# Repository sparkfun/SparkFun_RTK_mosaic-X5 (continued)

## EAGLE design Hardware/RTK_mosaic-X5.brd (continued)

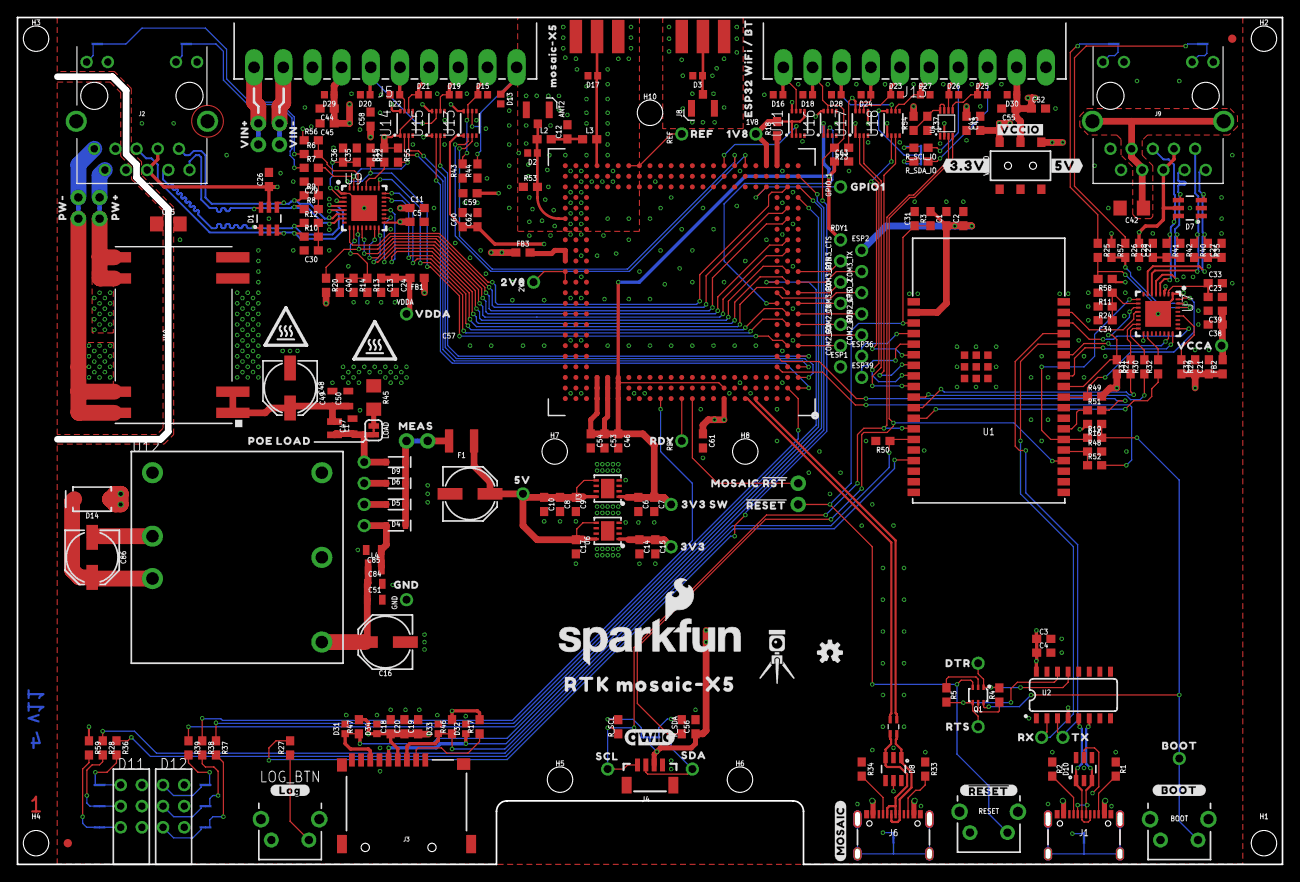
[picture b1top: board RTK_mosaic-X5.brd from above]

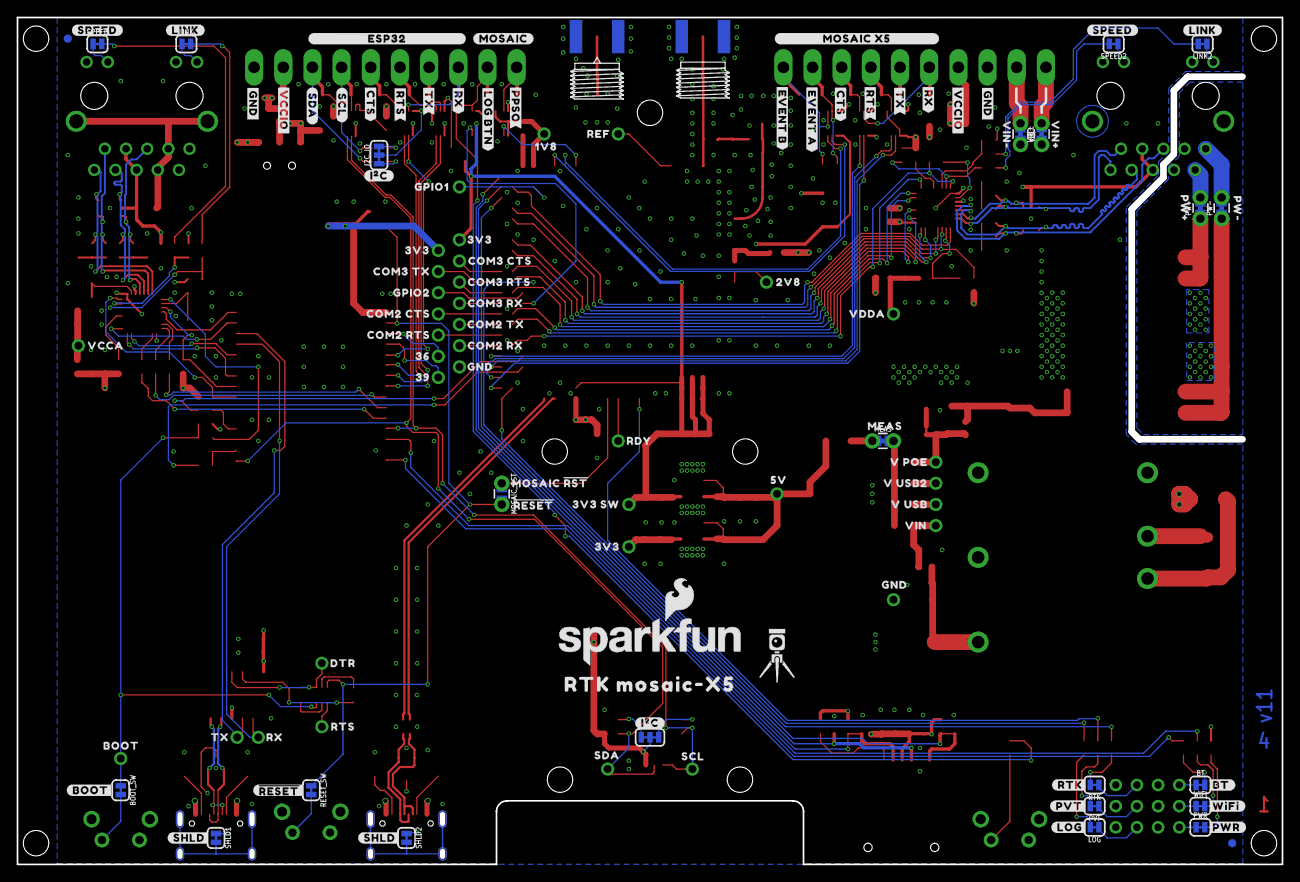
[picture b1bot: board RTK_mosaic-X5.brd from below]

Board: 4 copper layers, 151.8 x 101.6 mm, 408 parts (108 on the bottom side), 184 nets.

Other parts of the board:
LOGO2: QWIIC_LOGO_6MM; QWIIC_6MM
LOGO7: SFE_LOGO_NAME.2_INCH; SFE_LOGO_NAME_.2
LOGO8: SFE_LOGO_FLAME.2_INCH; SFE_LOGO_FLAME_.2
U$2: MOSAIC#X50
U$3, U$45: #SHLD#0
U$4, U$74: #RESET#0
U$5, U$113: PW#0
U$6, U$114: PW#1
U$7: ##RESET##5
U$8, U$46: #I�C#0
U$9, U$73: MOSAIC_#RST#6
U$10, U$120: #LINK#1
U$11: #LOG#4
U$12: #PVT#2
U$13: #RTK#3
U$14: #BT#2
U$15: #BOOT#6
U$16: #_______________MOSAIC_X5_______________#8
U$17, U$31: #RX#2
U$18, U$32: #TX#3
U$19, U$29: #RTS#4
U$20, U$30: #CTS#5
U$21: ESP32_WIFI_#_BT0
U$22: #EVENT_A#6
U$23: #EVENT_B#7
U$24, U$107: VCCA0
U$25, U$28: #GND#0
U$26, U$27, U$100: #VCCIO#1
U$33: #PPSO#11
U$34: #LOG_BTN#33
U$35: #SCL#10
U$36: #SDA#9
U$37, U$119: #MOSAIC#8
U$38: #___________________ESP32___________________#34
U$39: #3#3V#6
U$40: #5V#0
U$41, U$42: 2V8220
U$43, U$44: BOOT2
U$47: COM2_CTS219
U$48: COM2_RTS219
U$49: COM2_RX219
U$54: COM2_TX219
U$55, U$76: RTS2231
U$56, U$77: DTR2232
U$57: COM3_CTS18
U$58: COM3_RTS18
U$59, U$88: 3V3_SW25
U$60, U$87: 3V325
U$61, U$86: 5V25
U$62, U$84: MEAS2
U$63, U$70: VIN#0
U$64: COM3_RX219
U$65: COM3_TX18
U$66, U$67: GPIO17
U$68: GPIO218
U$69, U$99: RTK_MOSAIC#X50
U$71, U$72: VIN#1
U$75, U$78: RDY5
U$79, U$80: REF219
U$81: V_POE0
U$82: V_USB3
U$83: V_USB24
U$85: VIN1
U$89, U$90: RX0
U$91, U$92: SCL3
U$93, U$94: SDA4
U$95, U$96: TX1
U$97, U$98: VDDA220
U$101, U$102: 1V80
U$103: #PWR#0
U$104: #WIFI#1
U$105: 360
U$106: 39361
U$108: GND39362
U$109, U$110: 3V339362
U$116: #_LOG_#5
U$117: #_#RESET#_#0
U$118: #_BOOT_#1
U$121, U$122: #SPEED#0
U$135, U$143: GND12
U$136: POE_LOAD0
U$146, U$147: HIGH_TEMP_WARNING
U$152, U$153: RTK5#SVG0

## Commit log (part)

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2023-07-18 Ready for airwire review
2023-07-19 Silk added. Layer 15 polygon is now GND.
2023-07-19 Routed
2023-07-20 Tweaked and panelized
2023-07-20 Add panels
2023-07-20 Correct Ethernet PHY pad numbering. Needs re-panelizing
2023-07-21 Add second antenna connector for future mosaic-H product
2023-07-21 Adding u.FL connector for mosaic-H - with standoff holes for a u.FL-SMA daughter board
2023-07-24 Add Phy PROD_ID. Ready for manufacture
2023-08-31 V10 PCB - routed
2023-09-01 v10 - ready for manufacture
2023-09-01 Add datasheets
2023-09-05 Update front panel with new 1.3" OLED
2023-09-12 Add WiFi Basic example - tested with ESP IDF v5.1.1
2023-09-13 Rename WiFi STN example. Add OLED code
2023-09-14 Add STN BT Provisioning example - OLED QR Code display is WIP
2023-09-17 Remove LVGL. Add SSD1306
2023-09-17 Working OLED text and QR code
2023-09-18 BT Prov example: display IP address; add binaries
2023-09-19 Add RTK_mosaic-X5_Firmware
2023-09-20 X5 COM4 UART GGA working
2023-09-21 Ethernet DHCP + WiFi AP DHCP Bridge : almost working
2023-09-21 KISS - two modes: WiFi Bridge and UART GGA
2023-09-24 Better NMEA parsing. Default to NULL password
2023-09-24 Change ssid and password. Display IP address in mode 2
2023-09-25 Change console task stack size to 4K
2023-09-28 Add extra test sketches
2023-09-28 Swap mode 1 and 2. Rename. Display GGA in both modes
2023-09-29 Add x5_not_ready and oled_ready. Add .bat files
2023-10-05 Initial docs commit. Still WIP
2023-10-06 More docs updates
2023-10-08 RTK Base docs updates
2023-10-09 Add stickers v1
2023-10-09 Add OPUS results
2023-10-11 Add Correction Service
2023-10-12 Add ntrip_server
2023-10-12 Add firmware production test - exercise unused 'UART' pins
2023-10-13 docs updates
2023-10-13 Move BT Prov example
2023-10-13 Update BT Prov example - correct OLED address
2023-10-13 Don't ignore build
2023-10-17 Update ntrip_client
2023-11-02 Image links
    Modifies hyperlinks for images to `hookup_guide` folder
2023-11-06 Update QR codes
    Update QR codes to product page and hookup guide
2023-11-08 Add better connection images
2023-11-09 test page
    Updated indentation to work more smoothly
    Modified list types
2023-11-09 code changes
    changed admonition to terminal
    set code block syntax to bash
    fixed indentation on code block
2023-11-10 Update Lists
    Update the lists for the Quick Start instructions
2023-11-10 Add Septentrio Logo
2023-11-13 Fix USB section
    Fix definition list in USB section
    Convert background in image to transparent
    - matches other images in dark mode
2023-11-13 Fix Admonition
    Removes extra indent on the CH340 Driver section
2023-11-14 Dark Mode
    Modified the hardware pictures to use a transparent background to be easier on the eye when viewed in dark mode.
2023-11-21 Add logos
    Adds Septentrio and Espressif logos
2023-11-21 Enable footnotes
2023-11-21 Fix emojis
    Update emoji extension
2023-11-21 Update tabs
    Enables titled anchors for tabs
2023-11-21 Update mkdocs.yml
    Add new highlighting method
2023-11-21 Update privacy settings
    Open external links in new tab
2023-11-21 Update hardware_overview.md
    Re arrange power sections
2023-11-21 Update images
2024-01-03 Move component documentation
2024-01-03 Add drawings for enclosure and antenna dimensions
2024-01-03 Fix typos
2024-01-03 Add product image
2024-01-03 Fix build error
2024-01-03 Update mkdocs.yml
    Remove commented lines
2024-01-27 Add quick start guide
2024-01-27 Add image compression
    Reduces image file sizes during build
    Helps with web page size on load
2024-01-27 Update mkdocs.yml
    monorepo issue fixed
2024-01-27 Add dimensions for enclosure
2024-01-27 Baseline data for accuracy
2024-01-27 Add assembly pictures
2024-01-27 Add images of enclosure panels
2024-01-27 Hookup guide (final draft)
2024-01-27 Accent content tabs
    Accents added to fix white-on-white and dark-on-dark appearance as mentioned in this discussion: https://github.com/squidfunk/mkdocs-material/discussions/6699
2024-01-27 Add hookup guide thumbnail
    Action shot for product
2024-01-27 Update mkdocs.yml
    Re-enable commit/authors plugins
2024-01-27 Update mkdocs.yml
    Add root permission
2024-01-28 Update software_overview.md
    Add the WiFi instructions
2024-01-28 Basic formatting
2024-01-28 Update print_view.md
    Add missing sections
2024-01-28 Update mkdocs.yml
    Fix snippet indentation
2024-01-28 Fix Typos
    Fixes spelling, grammar, and syntax issues flagged by Grammarly plugin
2024-02-01 v1.0.1 - increase flow control memory
2024-02-01 Limit speed to 10M for ESP32 PHY (WiFi mode)
2024-02-01 v1.0.2 - remove escape sequence
2024-02-01 Move thumbnail image
2024-02-01 Update LICENSE.md
    Remove carriage returns
2024-02-01 Update mkdocs.yml
    Add Google analytics
    Update copyright year
2024-02-01 Update README.md
    Add documentation badges
2024-02-01 v1.0.3 - improved UART retries and timeouts
2024-02-01 Remove unused pictures
2024-02-01 Package contents
    Add packaging information
2024-02-01 Radio Instructions
2024-02-01 Grammar fixes
2024-02-01 Update README.md
    Link typo
2024-02-02 Update resources.md
    Use annotation to list article and video resources
2024-02-02 Add showcase video
2024-02-02 Updates for v1.1 PCB
2024-02-02 Fix rendering
2024-02-06 Update mkdocs.yml
    Fix hyperlink
2024-02-06 Update LICENSE.md
    Update copyright year
    Fix hyperlink and spacing
2024-02-12 Update extra.css
    Fix content tab aesthetic for titles including:
    - code blocks
    - keyboard buttons
2024-02-12 Update hardware_overview.md
    Fix typo in product link
2024-03-06 Update introduction.md
    Add GPS basics and Qwiic OLED tutorials
    Remove soldering tutorial (not required)
    Add RTK positioning blog post
    Add product comparison table
2024-03-08 Update product_video.png
    Fix video link
2024-03-08 Deployed 3fe5fcb with MkDocs version: 1.5.3
2024-06-01 Update resources.md
    Add QR code for hookup guide
    Add JammerTest blog post
2024-06-01 Update video CSS
2024-06-01 Deployed c778bbd with MkDocs version: 1.6.0
2024-08-08 Update product image
2024-08-08 Update product link
2024-08-19 Add a local copy of esptool.exe 4.6
2024-08-20 Update introduction.md
    Update product image
2024-08-20 Update favicon logo
    Renamed file
    Removed redundant image
2024-08-20 Update mkdocs.yml
    Update configuration
    - Add cookies consent/notification
    - Add previews
    - Add tooltips
    - Add code selection
    - Add disables for plugins (hosting)
2024-09-06 Update product image
    New product image link
2024-09-06 Deployed f715b47 with MkDocs version: 1.6.1
2024-10-18 Update Instructions
    Update the information for the L5 band:
    - Adds instructions for outputting RTCM messages for GPSL5 corrections
    Update note in NTRIP Server instructions
    - Adds admonition for click OK button
2024-10-18 Add instructions for Onocoy
    Adds instructions for mining rewards w/ Onocoy network
2024-10-18 Update README.md
    Fix link to product image
2024-10-18 Deployed a65c15a with MkDocs version: 1.6.1
2024-10-18 Update print_view.md
    Add Onocoy mining section to print out
2024-10-31 Deployed 8150470 with MkDocs version: 1.6.1
2024-10-31 Add rotated text
    Add styling for rotated (left/CCW) text in table
2024-10-31 Enable any GNSS signals
    Instructions updated for enabling any GNSS signal use, not just the GPS-L5 signal specifically
2024-12-31 Rename file
    Typo
2024-12-31 Update image links
2024-12-31 Update mkdocs.yml
    Fix typos
2024-12-31 Update workflow
    Update token
2024-12-31 Deployed e884774 with MkDocs version: 1.6.1
2025-06-25 v1.0.4 - WIP
2025-06-26 Add soft reset. Better use of uart_read_bytes. Pin uart task to core 1. Fewer static methods.
2025-06-26 Add firmware update instructions
2025-06-26 Deployed d75ca23 with MkDocs version: 1.6.1
2025-06-26 Deployed b469922 with MkDocs version: 1.6.1
2025-09-10 Replace <center> tag
2025-09-10 Replace icon
2025-09-10 Fix file name
2025-09-10 Update product comparison
2025-09-10 Update copyright year
2025-09-10 Update docs build
    Add icons
    Update build configuration
    - Remove git-authors plugin
    Update workflow
    Add javascript
    Update .gitignore
2025-09-10 Deployed 321aee8 with MkDocs version: 1.6.1
2025-09-10 Fix image name
2025-09-10 Deployed 8ec8242 with MkDocs version: 1.6.1
2025-09-12 Update component documentation
    Updates the firmware, datasheet, and manuals for the mosaic-X5
2025-09-15 Deployed 0160c57 with MkDocs version: 1.6.1
2025-09-15 Replace <sup> tag
    Replace <sup> tag with markdown notation
2025-09-15 Deployed 1804a45 with MkDocs version: 1.6.1
2026-04-22 Prep for v1.0.5 - support X5 firmware 4.15.1 - add Dockerfile
2026-04-23 Add yields to help avoid watchdog resets. Only wait for MAC address in WiFi mode
2026-04-23 Update version comments
2026-04-23 Update 4.15.1 info
2026-04-23 Deployed 01286b0 with MkDocs version: 1.6.1
2026-04-23 Fix quick_start refs
2026-04-23 Deployed fe00109 with MkDocs version: 1.6.1
2026-04-23 Correct docker lower case
2026-04-23 Update Dockerfile
2026-04-23 Correct assets/img
2026-04-23 Deployed 93a7475 with MkDocs version: 1.6.1
2026-04-23 Deployed 3cbabda with MkDocs version: 1.6.1
2026-04-23 Update bin files via Python
2026-04-23 Update screenshots
2026-04-23 Deployed 88e9c56 with MkDocs version: 1.6.1
2026-06-03 Remove MathJax and KaTeX support
2026-06-03 Update formatting
    Changes figcaption formatting
2026-06-03 Update forum links
2026-06-03 Update product links
    Use SEO links
2026-06-03 Update workflow
2026-06-03 Deployed 90da576 with MkDocs version: 1.6.1
2026-06-10 Add case and panel drawings and step files
2026-06-10 Deployed 82de239 with MkDocs version: 1.6.1
2026-06-10 Deployed 0a54058 with MkDocs version: 1.6.1
